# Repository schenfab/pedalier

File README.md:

View this project on [CADLAB.io](https://cadlab.io/project/1078). 

# pedalier
Hammond Organ MIDI pedal extension

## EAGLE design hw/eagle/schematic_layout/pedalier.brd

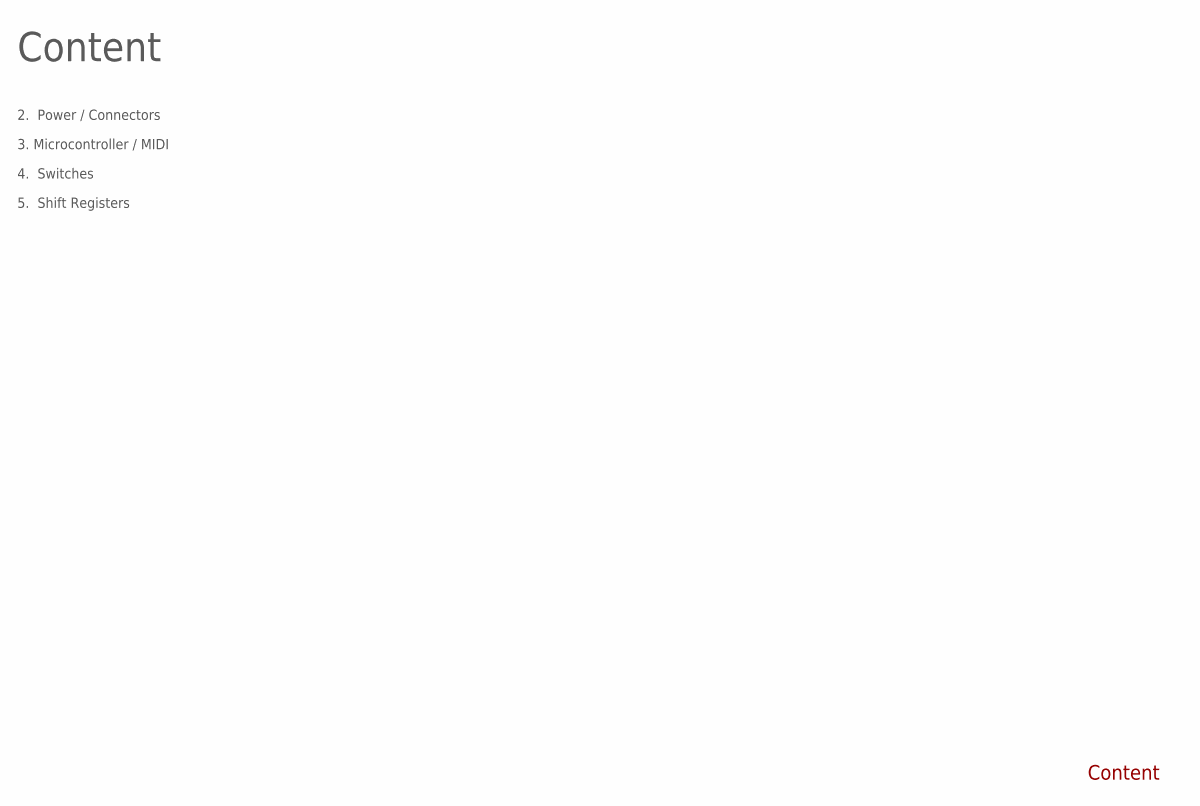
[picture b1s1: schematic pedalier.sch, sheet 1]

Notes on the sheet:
Content
2. Power / Connectors
3. Microcontroller / MIDI
4. Switches
5. Shift Registers

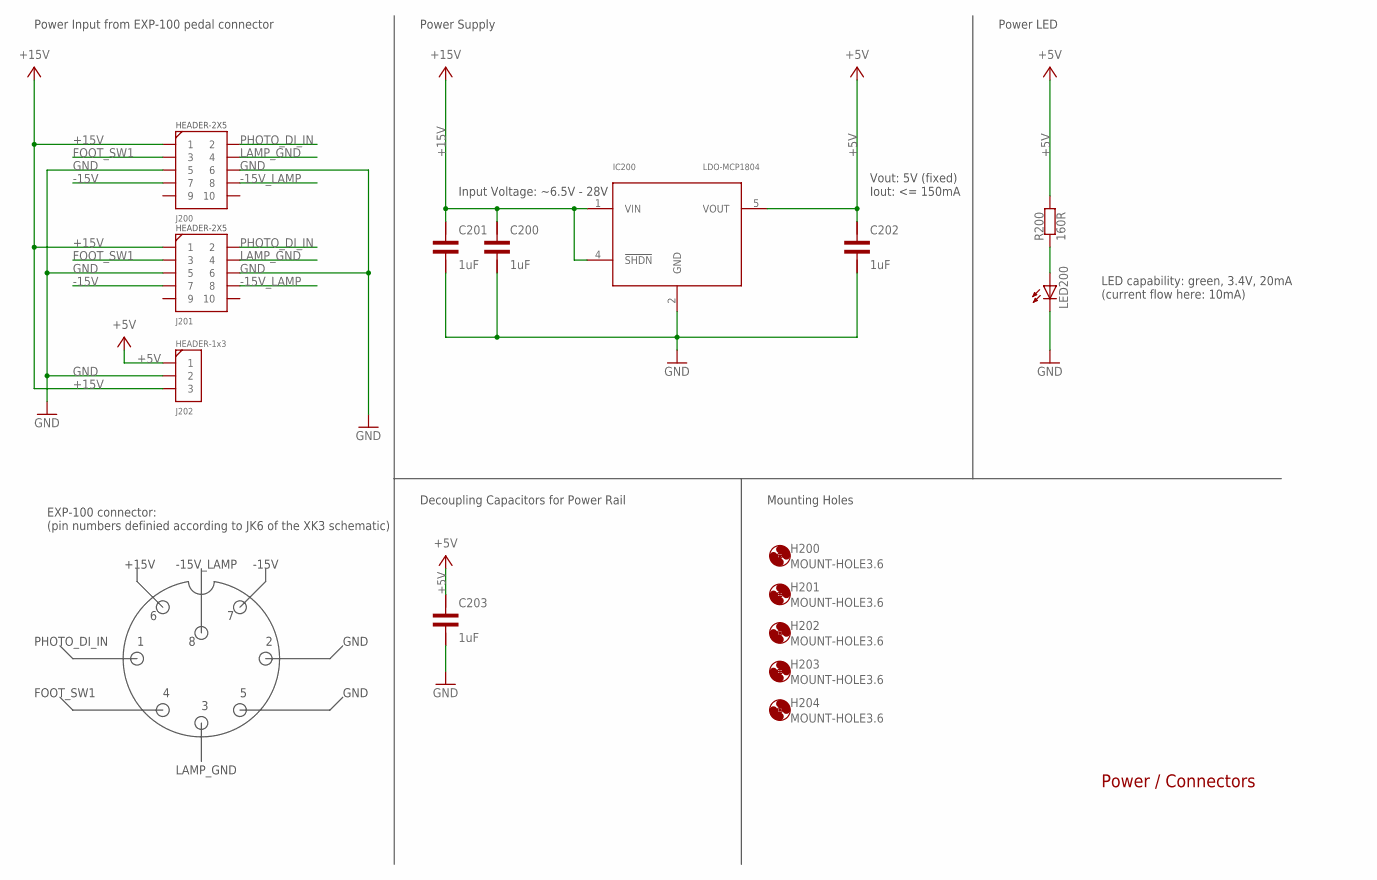
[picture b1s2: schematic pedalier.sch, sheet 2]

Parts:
C200, C201, C202, C203: 1uF; C1206
H200, H201, H202, H203, H204: MOUNT-HOLE3.6; 3,6
IC200: LDO-MCP1804; SOT23-5
J200, J201: HEADER-2X5
J202: HEADER-1X3
LED200: LED-BRIGHTEK; LED1206
R200: 160R; R1206

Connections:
+5V: C202.1, C203.1, IC200.5 (VOUT), J202.P$1 (1), R200.2; also elsewhere on the board
+15V: C200.1, C201.1, IC200.1 (VIN), IC200.4 (!SHDN), J200.P$1 (1), J201.P$1 (1), J202.P$3 (3)
-15V: J200.P$7 (7), J201.P$7 (7)
-15V_LAMP: J200.P$8 (8), J201.P$8 (8)
FOOT_SW1: J200.P$3 (3), J201.P$3 (3)
GND: C200.2, C201.2, C202.2, C203.2, IC200.2 (GND), J200.P$5 (5), J200.P$6 (6), J201.P$5 (5), J201.P$6 (6), J202.P$2 (2), LED200.P$1 (C); also elsewhere on the board
LAMP_GND: J200.P$4 (4), J201.P$4 (4)
unnamed: LED200.P$2 (A), R200.1
PHOTO_DI_IN: J200.P$2 (2), J201.P$2 (2)

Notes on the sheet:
Power / Connectors
Power Input from EXP-100 pedal connector
Power Supply
Power LED
Vout: 5V (fixed) Iout: <= 150mA
+15V
-15V
PHOTO_DI_IN
FOOT_SW1
LAMP_GND
GND
-15V_LAMP
EXP-100 connector: (pin numbers definied according to JK6 of the XK3 schematic)
LED capability: green, 3.4V, 20mA (current flow here: 10mA)
Decoupling Capacitors for Power Rail
Mounting Holes
Input Voltage: ~6.5V - 28V

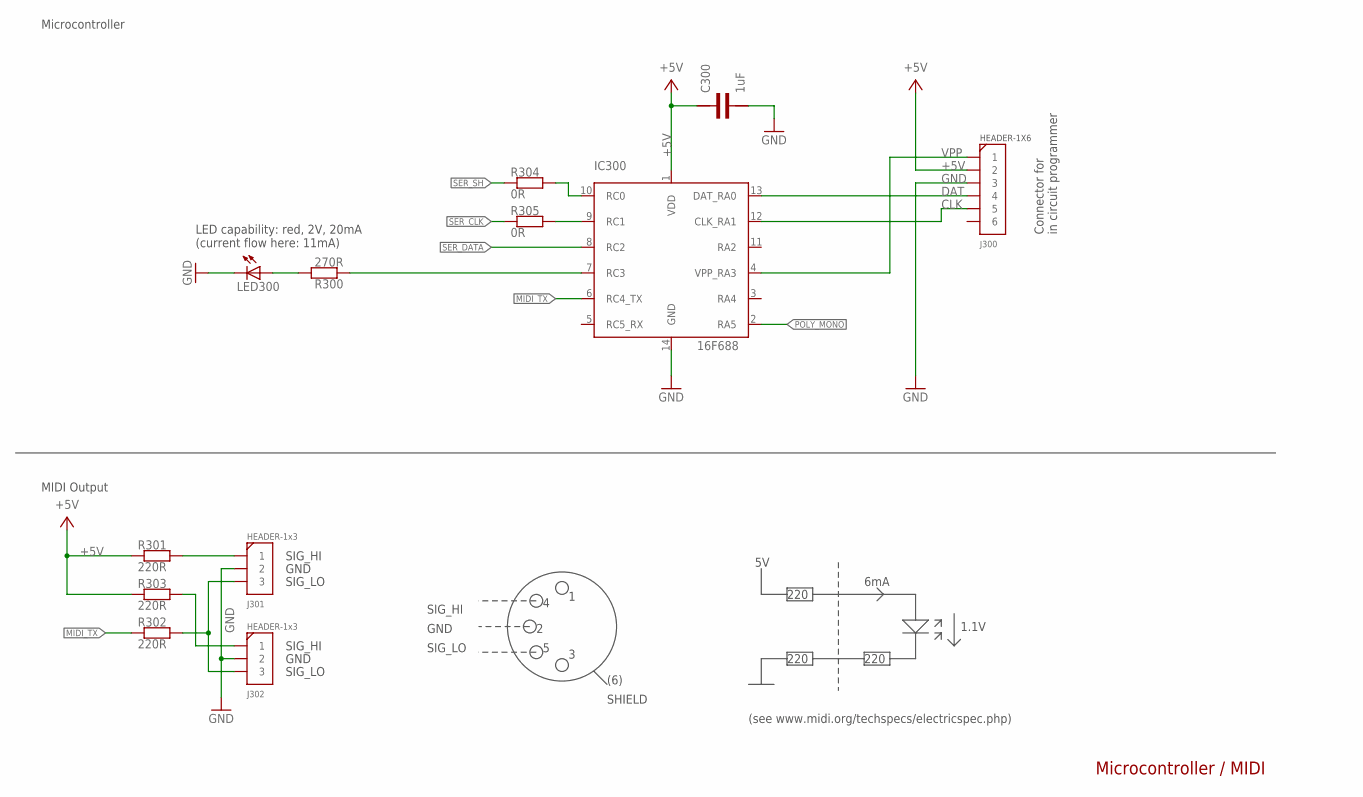
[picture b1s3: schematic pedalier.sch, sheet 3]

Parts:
C300: 1uF; C1206
IC300: PIC16F688SOIC14; SO14
J300: HEADER-1X6
J301, J302: HEADER-1X3
LED300: LED-BRIGHTEK; LED1206
R300: 270R; R1206
R301, R302, R303: 220R; R1206
R304, R305: 0R; R1206

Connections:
+5V: C300.1, IC300.1 (VDD), J300.P$2 (2), R301.1, R303.1; also elsewhere on the board
CLK: IC300.12 (CLK_RA1), J300.P$5 (5)
DAT: IC300.13 (DAT_RA0), J300.P$4 (4)
GND: C300.2, IC300.14 (GND), J300.P$3 (3), J301.P$2 (2), J302.P$2 (2), LED300.P$1 (C); also elsewhere on the board
MIDI_TX: IC300.6 (RC4_TX), R302.1
unnamed: J302.P$1 (1), R303.2
unnamed: LED300.P$2 (A), R300.2
unnamed: IC300.7 (RC3), R300.1
unnamed: J301.P$3 (3), J302.P$3 (3), R302.2
unnamed: J301.P$1 (1), R301.2
unnamed: IC300.10 (RC0), R304.2
unnamed: IC300.9 (RC1), R305.2
POLY_MONO: IC300.2 (RA5); also elsewhere on the board
SER_CLK: R305.1; also elsewhere on the board
SER_DATA: IC300.8 (RC2); also elsewhere on the board
SER_SH: R304.1; also elsewhere on the board
VPP: IC300.4 (VPP_RA3), J300.P$1 (1)

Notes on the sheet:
Microcontroller / MIDI
Connector for in circuit programmer
LED capability: red, 2V, 20mA (current flow here: 11mA)
Microcontroller
MIDI Output
(6)
(see www.midi.org/techspecs/electricspec.php)
SIG_LO
SIG_HI
GND
SHIELD
220
1.1V
6mA

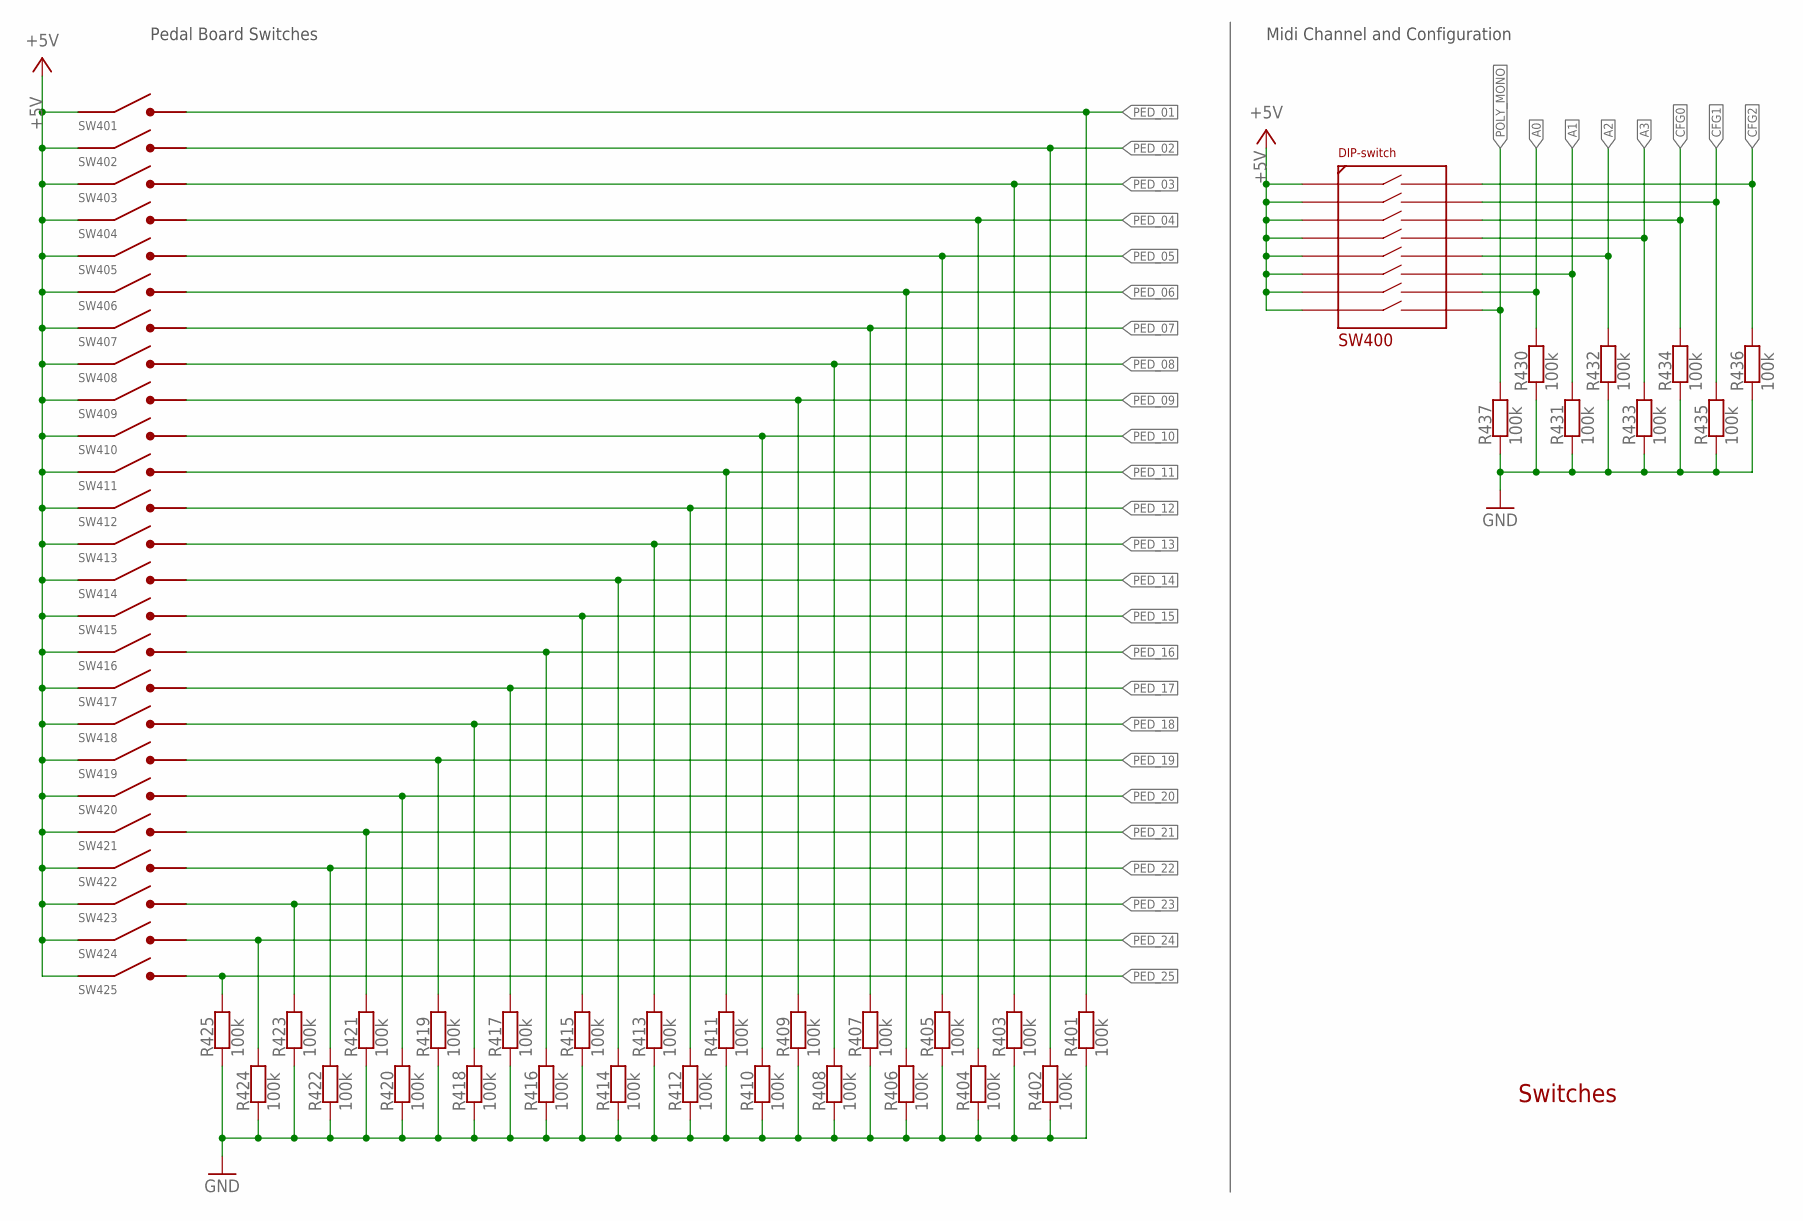
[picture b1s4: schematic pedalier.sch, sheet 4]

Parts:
R401, R402, R403, R404, R405, R406, R407, R408, R409, R410, R411, R412, R413, R414, R415, R416, R417, R418, R419, R420, R421, R422, R423, R424, R425, R430, R431, R432, R433, R434, R435, R436, R437: 100k; R1206
SW400: DIP-SW-8X; DIP-SW-8X-GULLWING
SW401, SW402, SW403, SW404, SW405, SW406, SW407, SW408, SW409, SW410, SW411, SW412, SW413, SW414, SW415, SW416, SW417, SW418, SW419, SW420, SW421, SW422, SW423, SW424, SW425: REED-SW; KSK-1A35-SMD

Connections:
+5V: SW400.P$1, SW400.P$3, SW400.P$5, SW400.P$7, SW400.P$9, SW400.P$11, SW400.P$13, SW400.P$15, SW401.1, SW402.1, SW403.1, SW404.1, SW405.1, SW406.1, SW407.1, SW408.1, SW409.1, SW410.1, SW411.1, SW412.1, SW413.1, SW414.1, SW415.1, SW416.1, SW417.1, SW418.1, SW419.1, SW420.1, SW421.1, SW422.1, SW423.1, SW424.1, SW425.1; also elsewhere on the board
A0: R430.2, SW400.P$14; also elsewhere on the board
A1: R431.2, SW400.P$12; also elsewhere on the board
A2: R432.2, SW400.P$10; also elsewhere on the board
A3: R433.2, SW400.P$8; also elsewhere on the board
CFG0: R434.2, SW400.P$6; also elsewhere on the board
CFG1: R435.2, SW400.P$4; also elsewhere on the board
CFG2: R436.2, SW400.P$2; also elsewhere on the board
GND: R401.1, R402.1, R403.1, R404.1, R405.1, R406.1, R407.1, R408.1, R409.1, R410.1, R411.1, R412.1, R413.1, R414.1, R415.1, R416.1, R417.1, R418.1, R419.1, R420.1, R421.1, R422.1, R423.1, R424.1, R425.1, R430.1, R431.1, R432.1, R433.1, R434.1, R435.1, R436.1, R437.1; also elsewhere on the board
PED_01: R401.2, SW401.2; also elsewhere on the board
PED_02: R402.2, SW402.2; also elsewhere on the board
PED_03: R403.2, SW403.2; also elsewhere on the board
PED_04: R404.2, SW404.2; also elsewhere on the board
PED_05: R405.2, SW405.2; also elsewhere on the board
PED_06: R406.2, SW406.2; also elsewhere on the board
PED_07: R407.2, SW407.2; also elsewhere on the board
PED_08: R408.2, SW408.2; also elsewhere on the board
PED_09: R409.2, SW409.2; also elsewhere on the board
PED_10: R410.2, SW410.2; also elsewhere on the board
PED_11: R411.2, SW411.2; also elsewhere on the board
PED_12: R412.2, SW412.2; also elsewhere on the board
PED_13: R413.2, SW413.2; also elsewhere on the board
PED_14: R414.2, SW414.2; also elsewhere on the board
PED_15: R415.2, SW415.2; also elsewhere on the board
PED_16: R416.2, SW416.2; also elsewhere on the board
PED_17: R417.2, SW417.2; also elsewhere on the board
PED_18: R418.2, SW418.2; also elsewhere on the board
PED_19: R419.2, SW419.2; also elsewhere on the board
PED_20: R420.2, SW420.2; also elsewhere on the board
PED_21: R421.2, SW421.2; also elsewhere on the board
PED_22: R422.2, SW422.2; also elsewhere on the board
PED_23: R423.2, SW423.2; also elsewhere on the board
PED_24: R424.2, SW424.2; also elsewhere on the board
PED_25: R425.2, SW425.2; also elsewhere on the board
POLY_MONO: R437.2, SW400.P$16; also elsewhere on the board

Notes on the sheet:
Switches
Pedal Board Switches
Midi Channel and Configuration

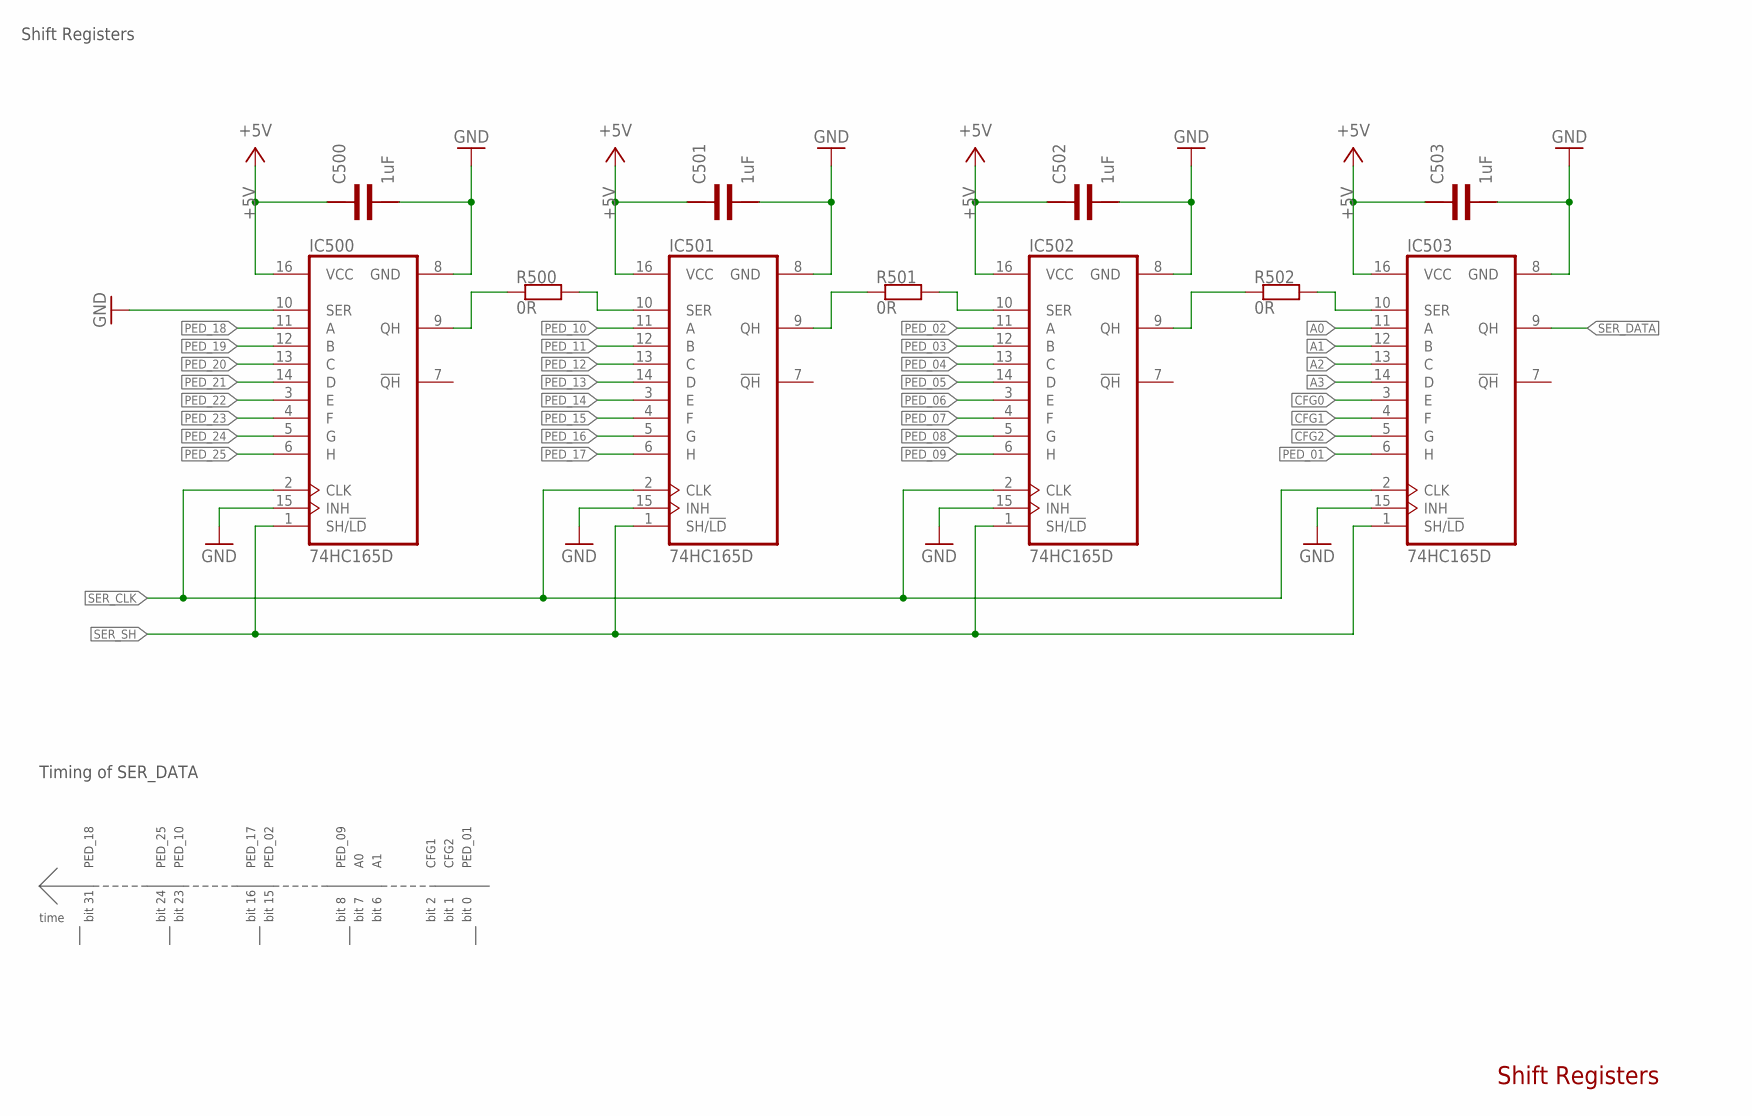
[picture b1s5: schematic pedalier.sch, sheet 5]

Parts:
C500, C501, C502, C503: 1uF; C1206
IC500, IC501, IC502, IC503: 74HC165D; SO16
R500, R501, R502: 0R; R1206

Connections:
+5V: C500.1, C501.1, C502.1, C503.1, IC500.16 (VCC), IC501.16 (VCC), IC502.16 (VCC), IC503.16 (VCC); also elsewhere on the board
A0: IC503.11 (A); also elsewhere on the board
A1: IC503.12 (B); also elsewhere on the board
A2: IC503.13 (C); also elsewhere on the board
A3: IC503.14 (D); also elsewhere on the board
CFG0: IC503.3 (E); also elsewhere on the board
CFG1: IC503.4 (F); also elsewhere on the board
CFG2: IC503.5 (G); also elsewhere on the board
GND: C500.2, C501.2, C502.2, C503.2, IC500.8 (GND), IC500.10 (SER), IC500.15 (INH), IC501.8 (GND), IC501.15 (INH), IC502.8 (GND), IC502.15 (INH), IC503.8 (GND), IC503.15 (INH); also elsewhere on the board
unnamed: IC500.9 (QH), R500.1
unnamed: IC501.9 (QH), R501.1
unnamed: IC502.10 (SER), R501.2
unnamed: IC502.9 (QH), R502.1
unnamed: IC503.10 (SER), R502.2
unnamed: IC501.10 (SER), R500.2
PED_01: IC503.6 (H); also elsewhere on the board
PED_02: IC502.11 (A); also elsewhere on the board
PED_03: IC502.12 (B); also elsewhere on the board
PED_04: IC502.13 (C); also elsewhere on the board
PED_05: IC502.14 (D); also elsewhere on the board
PED_06: IC502.3 (E); also elsewhere on the board
PED_07: IC502.4 (F); also elsewhere on the board
PED_08: IC502.5 (G); also elsewhere on the board
PED_09: IC502.6 (H); also elsewhere on the board
PED_10: IC501.11 (A); also elsewhere on the board
PED_11: IC501.12 (B); also elsewhere on the board
PED_12: IC501.13 (C); also elsewhere on the board
PED_13: IC501.14 (D); also elsewhere on the board
PED_14: IC501.3 (E); also elsewhere on the board
PED_15: IC501.4 (F); also elsewhere on the board
PED_16: IC501.5 (G); also elsewhere on the board
PED_17: IC501.6 (H); also elsewhere on the board
PED_18: IC500.11 (A); also elsewhere on the board
PED_19: IC500.12 (B); also elsewhere on the board
PED_20: IC500.13 (C); also elsewhere on the board
PED_21: IC500.14 (D); also elsewhere on the board
PED_22: IC500.3 (E); also elsewhere on the board
PED_23: IC500.4 (F); also elsewhere on the board
PED_24: IC500.5 (G); also elsewhere on the board
PED_25: IC500.6 (H); also elsewhere on the board
SER_CLK: IC500.2 (CLK), IC501.2 (CLK), IC502.2 (CLK), IC503.2 (CLK); also elsewhere on the board
SER_DATA: IC503.9 (QH); also elsewhere on the board
SER_SH: IC500.1 (SH/!LD), IC501.1 (SH/!LD), IC502.1 (SH/!LD), IC503.1 (SH/!LD); also elsewhere on the board

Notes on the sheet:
Shift Registers
CFG2
PED_01
PED_02
PED_09
PED_10
PED_17
PED_18
PED_25
time
bit 0
bit 1
bit 7
bit 6
bit 8
bit 15
bit 16
bit 23
bit 24
bit 31
Timing of SER_DATA
CFG1
bit 2

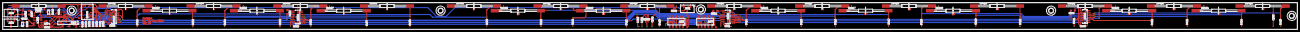
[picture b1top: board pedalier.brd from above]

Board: 2 copper layers, 970.0 x 20.0 mm, 97 parts (0 on the bottom side), 62 nets.

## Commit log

2015-04-27 Addition of hw and sw directories
2015-04-27 Implemented first version of the software: - Integration Test 1 working with mocked hardware - No PIC hardware access yet - No debounce and monophonic mode yet
2015-05-11 Todo for HwAbstraction: adapt to serial data order
2015-05-11 Addition of schematic, layout and gerber data
2015-05-11 Fix for serial data order
2015-05-14 Implemented second version of the software: - Buxfixes - Integration tests 1 and 2 working with mocked hardwrae - PIC HW access - No debounce yet (will only be implemented when needed) - Some todos l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
2015-05-14 Addition of build output for target platform: asm files and linked application as hex file
2015-06-09 Refactored config switches. Added dedicated switch for inversion of the pedal state.
2015-06-09 Change of the interface to hw_abstraction due to stack depth problems when compiling for PIC
2015-06-11 Increased oscillator frequency from 4MHz to 8MHz
2015-06-11 Removed unused method hwPeripherals_waitForTimer
2015-06-11 Added integration test for inverted pedals
2015-06-12 Added value for configuration word register
2015-06-12 Bugfix: the first data bit is already there before the first clock cycle
2015-06-12 The configuration word register is hardware specific
2015-06-12 Adapted integration tests to bugfix
2015-06-12 Configure all ports as digital (and not analog) inputs
2015-06-12 Fix for readSerialData and readMonoSwitch
2015-06-12 Adapted serial clock configuration to 8MHz system clock
2015-06-12 Productive build
2015-06-16 Moved pedal board one octave up (which is correct)
2018-05-24 Backlink to CADLAB.io has been added.

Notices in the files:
hw/eagle/schematic_layout/pedalier.brd:
GPL v3
